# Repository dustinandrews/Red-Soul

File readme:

Robotic Minion Starter Kit (Arduino Compatible)
http://authenticinvention.com/authentic/?post_type=landing_page&p=47

Codename: Red-Soul

License: http://creativecommons.org/licenses/by/3.0/

Eagle files, code and other files for an Arduino compatible platform.

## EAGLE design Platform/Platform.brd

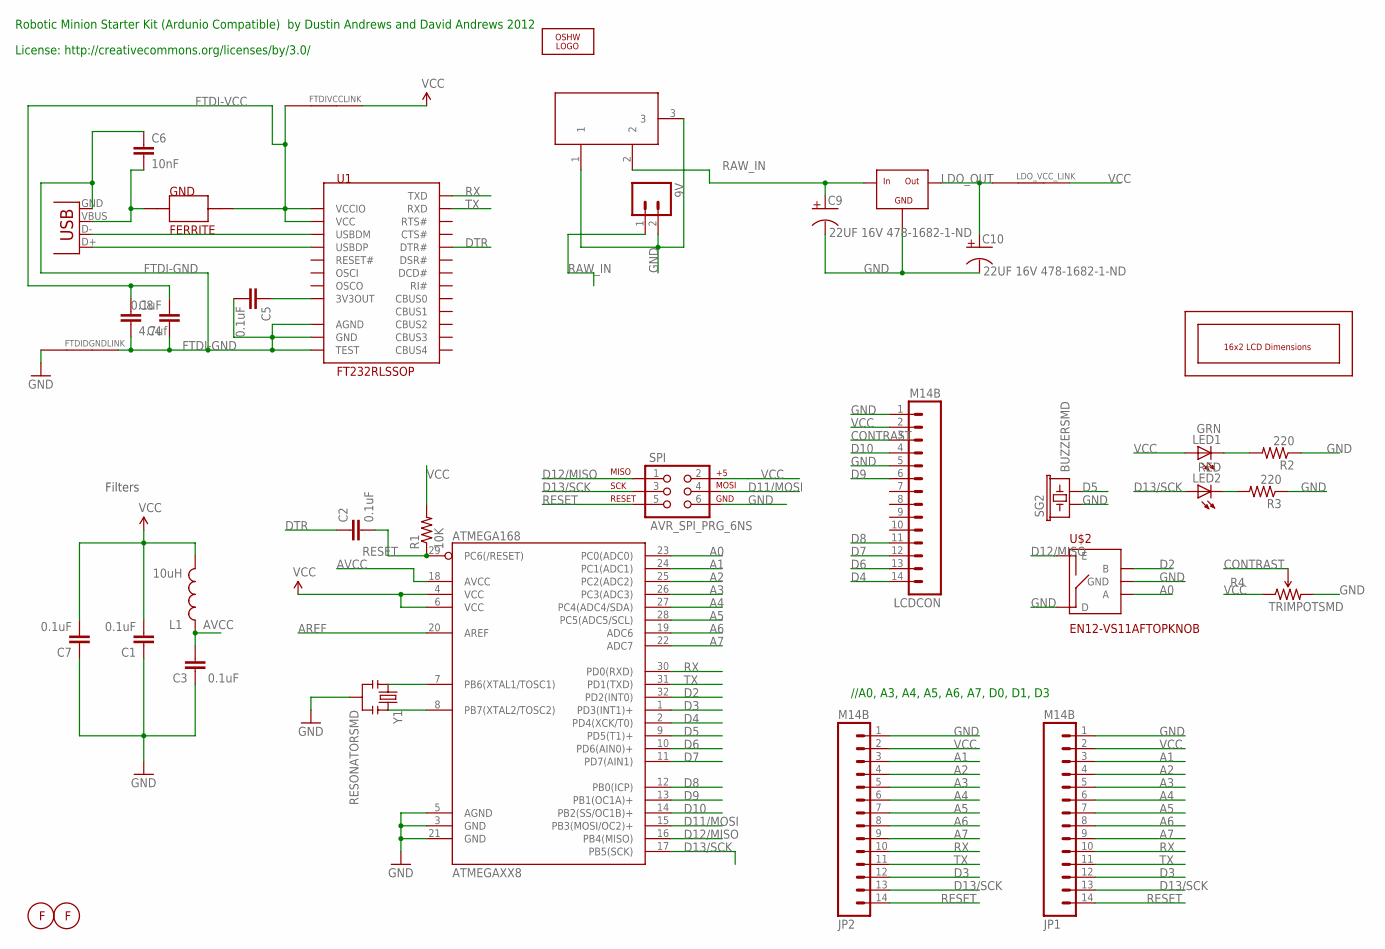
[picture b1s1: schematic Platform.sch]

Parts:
9V: M02PTH; 1X02
ATMEGAXX8: ATMEGA168; TQFP32-08; DIGIKEY# ATMEGA328-AU
C1, C2, C3, C4, C5, C7: 0.1uF; 0805; DIGIKEY# 478-1395-1-ND
C6: 10nF; C0805
C8: 4.7uf; 0805; DIGIKEY# 445-1369-1-ND
C9, C10: 22UF 16V 478-1682-1-ND; 1210POL; DIGIKEY# 478-1682-1-ND
FM1, FM2: FIDUCIAL1MM; 1MMCIRCLE
FTDIDGNDLINK: LINK; ISOLATOR
FTDIVCCLINK: LINK; ISOLATOR
GND: FERRITE; 0805; DIGIKEY# 240-2399-1-ND
J1: DC21MMX; DC-21MM
JP1, JP2: M14B; 1X14B
L1: 10uH; 0805; DIGIKEY# 587-2048-1-ND
LCDCON: M14B; 1X14B; DIGIKEY# 67-1781-ND
LDO_VCC_LINK: LINK; ISOLATOR
LED1: GRN; LED-0805; DIGIKEY# 754-1131-1-ND
LED2: RED; LED-0805; DIGIKEY# 475-1278-1-ND
LOGO1: OSHW_LOGO_10MILX0750-NT; OSHW_10X750_NOTEXT
R1: 10K; 0805; DIGIKEY# RHM10.0KAECT-ND
R2, R3: 220; 0805; DIGIKEY# RHM220AECT-ND
R4: TRIMPOTSMD; TRIMPOT-3MM; DIGIKEY# 490-4611-1-ND
SG2: BUZZERSMD; BUZZER-CMT1603; DIGIKEY# 668-1110-1-ND
SPI: AVR_SPI_PRG_6NS; 2X3-NS
U1: FT232RLSSOP; SSOP28; DIGIKEY# 768-1007-1-ND
U$1: IFX25001TC; TO263-3; DIGIKEY# IFX25001TC V50INCT-ND
U$2: EN12-VS11AFTOPKNOB; 12MM_ROTATY_TOP; DIGIKEY# 987-1194-ND
U$3: LCM-S01602DTR; LCD16X2
X1: USBSMD; USB-MINIB; DIGIKEY# ED2992CT-ND
Y1: RESONATORSMD; RESONATOR-SMD; DIGIKEY# 490-1198-1-ND

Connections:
3V3OUT: C5.1, U1.17 (3V3OUT)
A0: ATMEGAXX8.23 (PC0(ADC0)), U$2.A
A1: ATMEGAXX8.24 (PC1(ADC1)), JP1.3, JP2.3
A2: ATMEGAXX8.25 (PC2(ADC2)), JP1.4, JP2.4
A3: ATMEGAXX8.26 (PC3(ADC3)), JP1.5, JP2.5
A4: ATMEGAXX8.27 (PC4(ADC4/SDA)), JP1.6, JP2.6
A5: ATMEGAXX8.28 (PC5(ADC5/SCL)), JP1.7, JP2.7
A6: ATMEGAXX8.19 (ADC6), JP1.8, JP2.8
A7: ATMEGAXX8.22 (ADC7), JP1.9, JP2.9
AREF: ATMEGAXX8.20 (AREF)
AVCC: ATMEGAXX8.18 (AVCC), C3.2, L1.1
CONTRAST: LCDCON.3, R4.2 (WIPER)
D2: ATMEGAXX8.32 (PD2(INT0)), U$2.B
D3: ATMEGAXX8.1 (PD3(INT1)+), JP1.12, JP2.12
D4: ATMEGAXX8.2 (PD4(XCK/T0)), LCDCON.14
D5: ATMEGAXX8.9 (PD5(T1)+), SG2.P$2 (2)
D6: ATMEGAXX8.10 (PD6(AIN0)+), LCDCON.13
D7: ATMEGAXX8.11 (PD7(AIN1)), LCDCON.12
D8: ATMEGAXX8.12 (PB0(ICP)), LCDCON.11
D9: ATMEGAXX8.13 (PB1(OC1A)+), LCDCON.6
D10: ATMEGAXX8.14 (PB2(SS/OC1B)+), LCDCON.4
D11/MOSI: ATMEGAXX8.15 (PB3(MOSI/OC2)+), SPI.4
D12/MISO: ATMEGAXX8.16 (PB4(MISO)), SPI.1, U$2.E
D13/SCK: ATMEGAXX8.17 (PB5(SCK)), JP1.13, JP2.13, LED2.A, SPI.3
D+: U1.15 (USBDP), X1.D+
D-: U1.16 (USBDM), X1.D-
DTR: C2.1, U1.2 (DTR#)
FTDI-GND: C4.1, C5.2, C6.1, C8.2, FTDIDGNDLINK.P$2, U1.7 (GND), U1.18 (GND), U1.21 (GND), U1.25 (AGND), U1.26 (TEST), X1.GND
FTDI-VCC: C4.2, C8.1, FTDIVCCLINK.P$1, GND.2, U1.4 (VCCIO), U1.20 (VCC)
GND: 9V.2, ATMEGAXX8.3 (GND), ATMEGAXX8.5 (AGND), ATMEGAXX8.21 (GND), C1.1, C3.1, C7.1, C9.2 (-), C10.2 (-), FTDIDGNDLINK.P$1, J1.1, J1.3, JP1.1, JP2.1, LCDCON.1, LCDCON.5, R2.1, R3.1, R4.3 (CW), SG2.P$1 (1), SPI.6, U$1.2 (GND), U$1.TAB (GND), U$2.C (GND), U$2.D, Y1.2
LDO_OUT: C10.1 (+), LDO_VCC_LINK.P$1, U$1.3 (OUT)
unnamed: LED2.C, R3.2
unnamed: LED1.C, R2.2
RAW_IN: 9V.1, C9.1 (+), J1.2, U$1.1 (IN)
RESET: ATMEGAXX8.29 (PC6(/RESET)), C2.2, JP1.14, JP2.14, R1.1, SPI.5
RX: ATMEGAXX8.30 (PD0(RXD)), JP1.10, JP2.10, U1.1 (TXD)
TX: ATMEGAXX8.31 (PD1(TXD)), JP1.11, JP2.11, U1.5 (RXD)
VBUS: C6.2, GND.1, X1.VBUS
VCC: ATMEGAXX8.4 (VCC), ATMEGAXX8.6 (VCC), C1.2, C7.2, FTDIVCCLINK.P$2, JP1.2, JP2.2, L1.2, LCDCON.2, LDO_VCC_LINK.P$2, LED1.A, R1.2, R4.1 (CCW), SPI.2
XTAL1: ATMEGAXX8.7 (PB6(XTAL1/TOSC1)), Y1.1
XTAL2: ATMEGAXX8.8 (PB7(XTAL2/TOSC2)), Y1.3

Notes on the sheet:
Filters
//A0, A3, A4, A5, A6, A7, D0, D1, D3
Robotic Minion Starter Kit (Ardunio Compatible) by Dustin Andrews and David Andrews 2012
License: http://creativecommons.org/licenses/by/3.0/

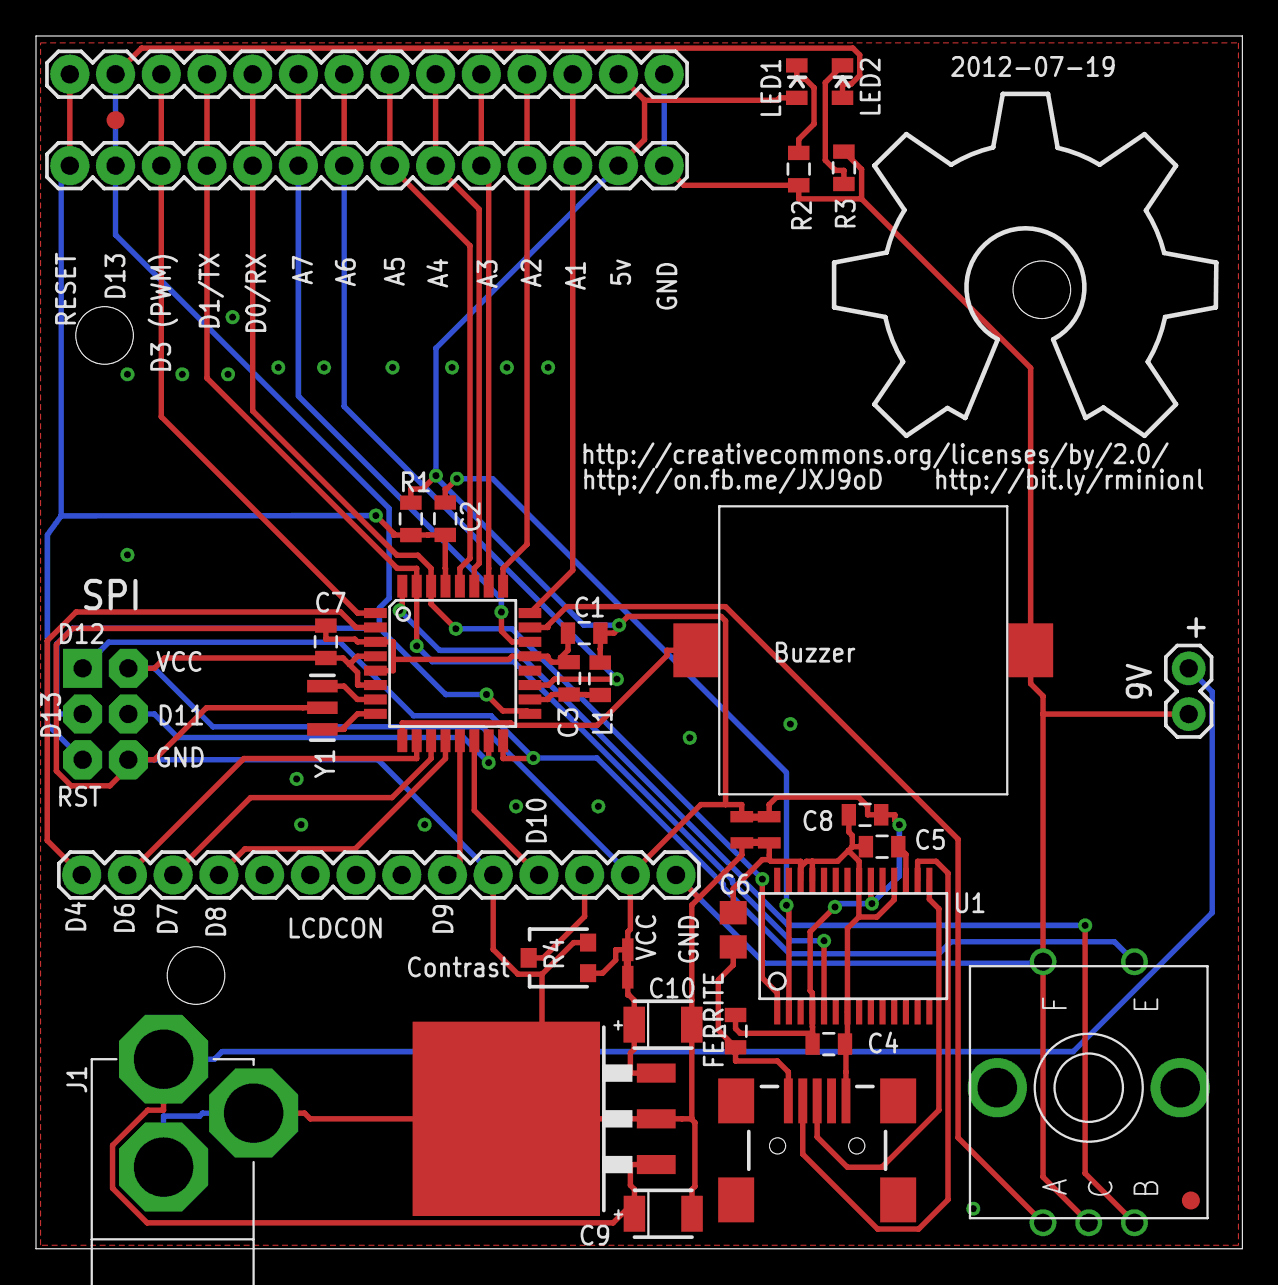
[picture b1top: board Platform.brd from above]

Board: 2 copper layers, 67.0 x 67.4 mm, 38 parts (0 on the bottom side), 40 nets.

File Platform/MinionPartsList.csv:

Quant,Digikey#,Name,Value,Desc
1,240-2399-1-ND,FERRITE,FERRITE,
1,445-1369-1-ND,CAP0805,4.7uf,Capacitor
1,475-1278-1-ND,LED0805,RED,LEDs
1,478-1383-1-ND,CAP_POL,0.01uf,Polarized Capacitor
5,478-1395-1-ND,CAP0805,0.1uF,Capacitor
2,478-1682-1-ND,CAP_POL1210,22UF 16V  478-1682-1-ND,Polarized Capacitor
1,490-1198-1-ND,RESONATORSMD,RESONATORSMD,Resonator
1,490-4611-1-ND,TRIMPOTSMD,TRIMPOTSMD,
1,587-2048-1-ND,INDUCTOR0805,10uH,Inductors
1,668-1110-1-ND,BUZZERSMD,BUZZERSMD,Buzzer 12mm
1,754-1131-1-ND,LED0805,GRN,LEDs
1,768-1007-1-ND,FT232RLSSOP,FT232RLSSOP,FT232RL
1,987-1194-ND,EN12-VS11AFTOPKNOB,EN12-VS11AFTOPKNOB,12mm Rotary Encoder with switch
1,ATMEGA328-AU,ATMEGA168,ATMEGA168,
1,CP-002APJCT-ND,DCJACKSMD,DCJACKSMD,
1,ED2992CT-ND,USBSMD,USBSMD,USB Connectors
1,IFX25001TC V50INCT-ND,IFX25001TC,IFX25001TC,IC REG LDO 5.0V 400MA TO263-3
1,RHM10.0KAECT-ND,RESISTOR0805-RES,10K,Resistor
2,RHM220AECT-ND,RESISTOR0805-RES,220 ohm,Resistor
1,67-1781-ND,16x2 LCD,,

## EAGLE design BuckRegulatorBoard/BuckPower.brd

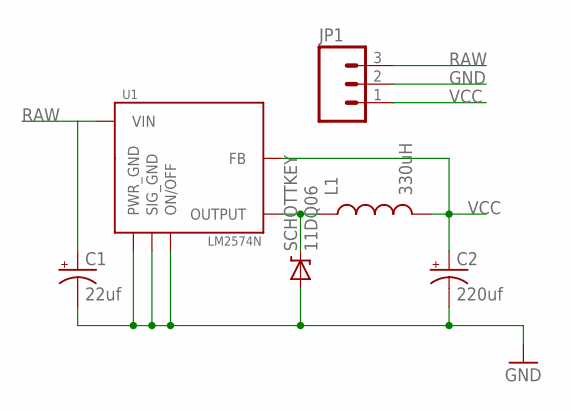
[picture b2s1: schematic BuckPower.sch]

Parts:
C1: 22uf; CPOL-RADIAL-100UF-25V
C2: 220uf; CPOL-RADIAL-100UF-25V
JP1: M031X03_NO_SILK; 1X03_NO_SILK
L1: 330uH; INDUCTOR-1206
SCHOTTKEY: 11DQ06; DIODE-ZENER
U1: LM2574N; 8DILL

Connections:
GND: C1.2 (-), C2.2 (-), JP1.2, SCHOTTKEY.P$2 (A), U1.2 (SIG_GND), U1.3 (ON/OFF), U1.4 (PWR_GND)
unnamed: L1.P$1 (1), SCHOTTKEY.P$1 (C), U1.7 (OUTPUT)
RAW: C1.1 (+), JP1.3, U1.5 (VIN)
VCC: C2.1 (+), JP1.1, L1.P$2 (2), U1.1 (FB)

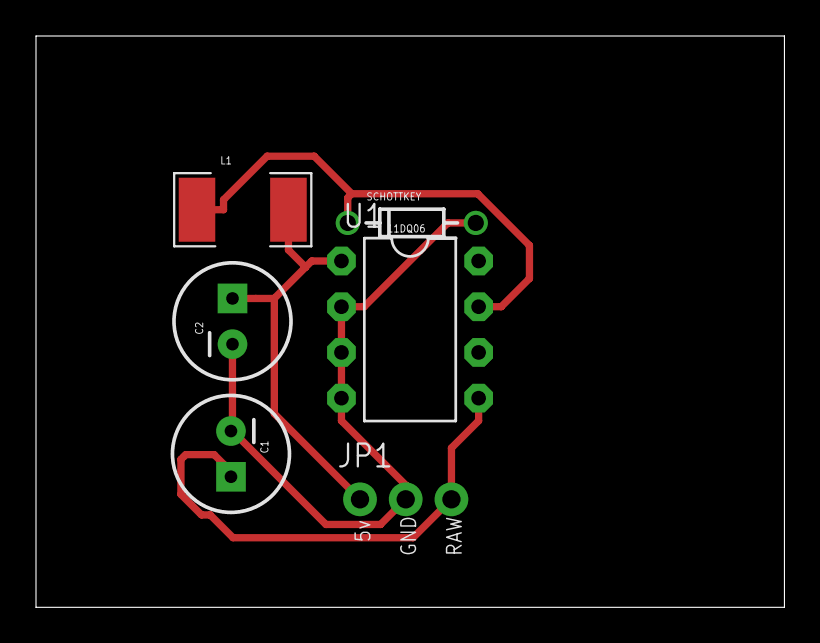
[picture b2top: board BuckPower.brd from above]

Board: 2 copper layers, 41.6 x 31.7 mm, 6 parts (0 on the bottom side), 4 nets.

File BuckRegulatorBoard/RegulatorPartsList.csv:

1,Switching regulator,LM2574N-5.0-ND,1.12
1,CAP ALUM 22UF 50V 20% RADIAL,399-6108-ND,0.0557
1,CAP ALUM 220UF 16V 20% RADIAL 10V 20% SMD,P5139-ND,0.0955
1,DIODE SCHOTTKY 60V 1.1A DO-41,11DQ06-ND,0.3052
1,INDUCTOR 330UH 10% 1207 SMD,587-3084-1-ND,0.1085
,,,1.6849

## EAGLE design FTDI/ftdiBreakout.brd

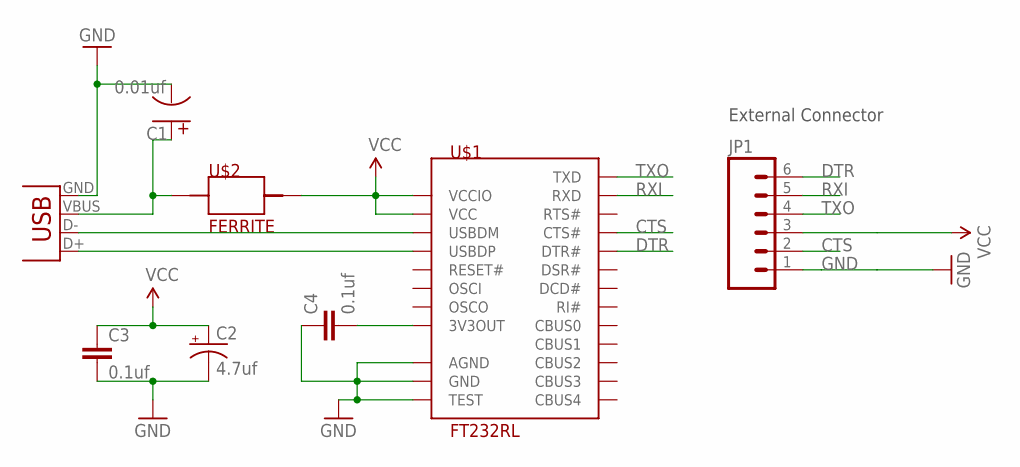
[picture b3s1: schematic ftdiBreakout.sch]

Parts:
C1: 0.01uf; 0805POL
C2: 4.7uf; CPOL-RADIAL-100UF-25V
C3, C4: 0.1uf; 0805
JP1: M06SIP; 1X06
U$1: FT232RL; TSSOP28
U$2: FERRITE; 0805
X1: USBSMD; USB-MINIB

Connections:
CTS: JP1.2, U$1.11 (CTS#)
DTR: JP1.6, U$1.2 (DTR#)
GND: C1.-, C2.2 (-), C3.2, C4.1, JP1.1, U$1.7 (GND), U$1.18 (GND), U$1.21 (GND), U$1.25 (AGND), U$1.26 (TEST), X1.GND
unnamed: C1.+, U$2.1, X1.VBUS
unnamed: U$1.16 (USBDM), X1.D-
unnamed: U$1.15 (USBDP), X1.D+
unnamed: C4.2, U$1.17 (3V3OUT)
RXI: JP1.5, U$1.5 (RXD)
TXO: JP1.4, U$1.1 (TXD)
VCC: C2.1 (+), C3.1, JP1.3, U$1.4 (VCCIO), U$1.20 (VCC), U$2.2

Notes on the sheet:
External Connector

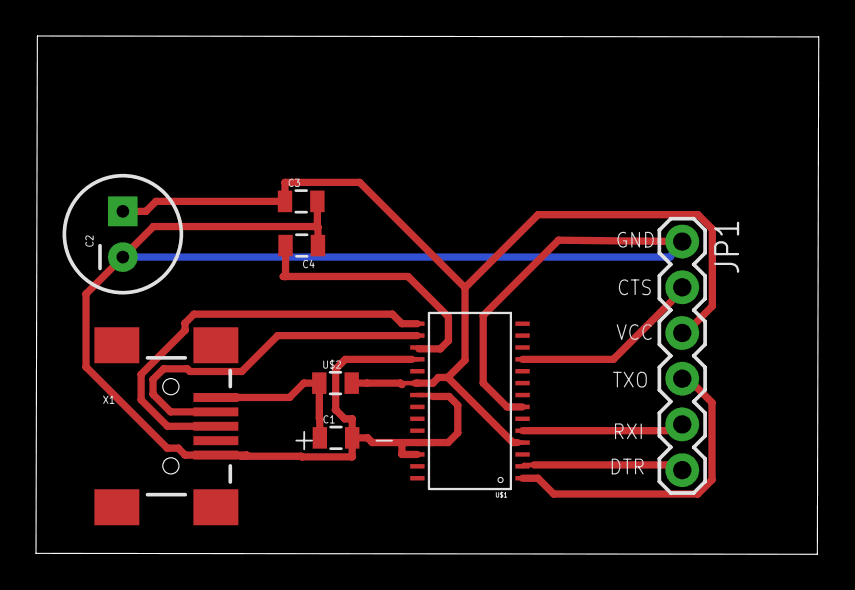
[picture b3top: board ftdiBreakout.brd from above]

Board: 2 copper layers, 43.5 x 28.8 mm, 8 parts (0 on the bottom side), 10 nets.

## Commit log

2012-04-11 fixed up design rules. Copied the actual newest boards into t the project
2012-04-13 added barrel connector and touched up top silk
2012-04-16 updated component locations and traces
2012-04-17 More board tweak, added part list and toner file used to make pre prototype 2
2012-04-17 Cad files added
2012-04-22 Tested versions of breakout boards
2012-04-22 added breakout boards parts lists
2012-05-02 prototype 3
2012-05-03 Fixed some issues with the FTDI. Created Gerbers. Sent version off for manufacture.
2012-05-13 updates from prototype 3
2012-05-13 updated parts list
2012-05-15 prototype 4
2012-05-22 Fixed typo and terminal spacing.
2012-05-22 Updated Gerbers
2012-05-22 fixed error in parts list
2012-06-05 switched back to LDO
2012-06-06 wiring traces added
2012-06-06 Added DIGIKEY# attribute to parts and generated BOM
2012-06-08 added dimensions, reference drawing for lcd
2012-06-12 imported cam file and created a dimensions doc
2012-06-14 Prototype 5 changes
2012-07-08 Added enclosure drawing
2012-07-08 Really added drawing of enclosure and updated the silk screen on the board.
2012-07-20 Better filter placement and moved 9v terminal to a better spot
2012-07-24 Latest tweaks to enclosure
2012-07-24 Added demo Arduino sketch
2012-07-26 Update Platform/RoboticMinionEnclosure.svg
    Manually merged changes that got messed up with an -amend. Don't use that anymore!
2012-08-04 Final Design for Production
2012-08-09 Moved silkscreen off mounting holes
2012-09-12 Update Platform/Sketch/Minion/Minion.ino
    Added license and documentation on needed library files.

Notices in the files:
Platform/Platform.brd:
http://creativecommons.org/licenses/by/2.0
parts and their libraries:
SparkFun: Licensing: CC v3.0 Share-Alike You are welcome to use this library for commercial purposes.
